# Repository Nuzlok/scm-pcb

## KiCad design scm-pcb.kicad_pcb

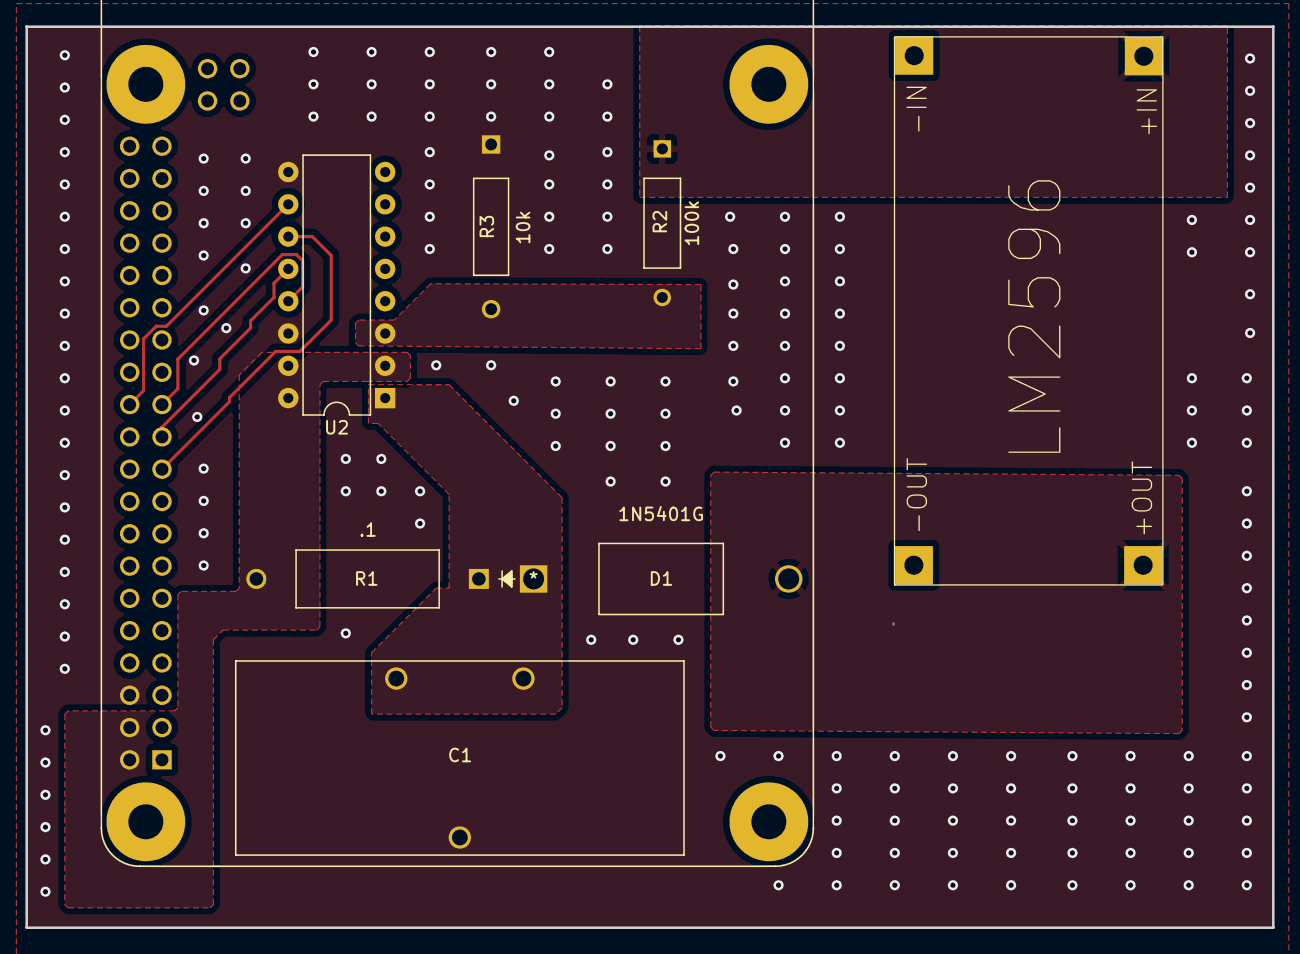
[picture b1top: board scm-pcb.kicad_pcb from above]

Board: 2 copper layers, 98.0 x 70.9 mm, 7 parts (0 on the bottom side), 8 nets.

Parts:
C1: C; MAL219690102E3
D1: 1N5401G
J1: Raspberry_Pi_2_3; MODULE_RASPBERRY_PI_3_MODEL_B+
R1: .1; PAC100001007FA1000
R2: 100k; MFR-25FRF52-100K
R3: 10k; CMF5510K000FKEB
U2: MCP3008; DIP-16_W7.62mm

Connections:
GND: C1.1, J1.6 (GND), R3.1, U2.9 (DGND), U2.14 (AGND)
unnamed: J1.2 (5V), J1.4 (5V), R1.2, U2.2 (CH1), U2.15 (Vref), U2.16 (Vdd)
unnamed: C1.2, C1.3, D1.1 (K), R1.1, U2.1 (CH0)
unnamed: J1.21 (MISO0/GPIO9), U2.12 (Dout)
unnamed: J1.19 (MOSI0/GPIO10), U2.11 (Din)
unnamed: J1.23 (SCLK0/GPIO11), U2.13 (CLK)
unnamed: J1.24 (~CE0/GPIO8), U2.10 (~CS/SHDN)
unnamed: R2.2, R3.2, U2.3 (CH2)

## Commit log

2023-03-13 Init commit
2023-03-13 Updated PCB
2023-03-17 Added ground via and cut corners (literally)
2023-04-26 final commit
2023-04-28 final edits

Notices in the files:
parts and their libraries:
Copyright 2021 Accelerated Designs. All rights reserved.
